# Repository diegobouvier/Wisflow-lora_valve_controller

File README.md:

# Wisflow-lora_valve_controller
Kicad proyecto for a LoRa remote valve controler actuator

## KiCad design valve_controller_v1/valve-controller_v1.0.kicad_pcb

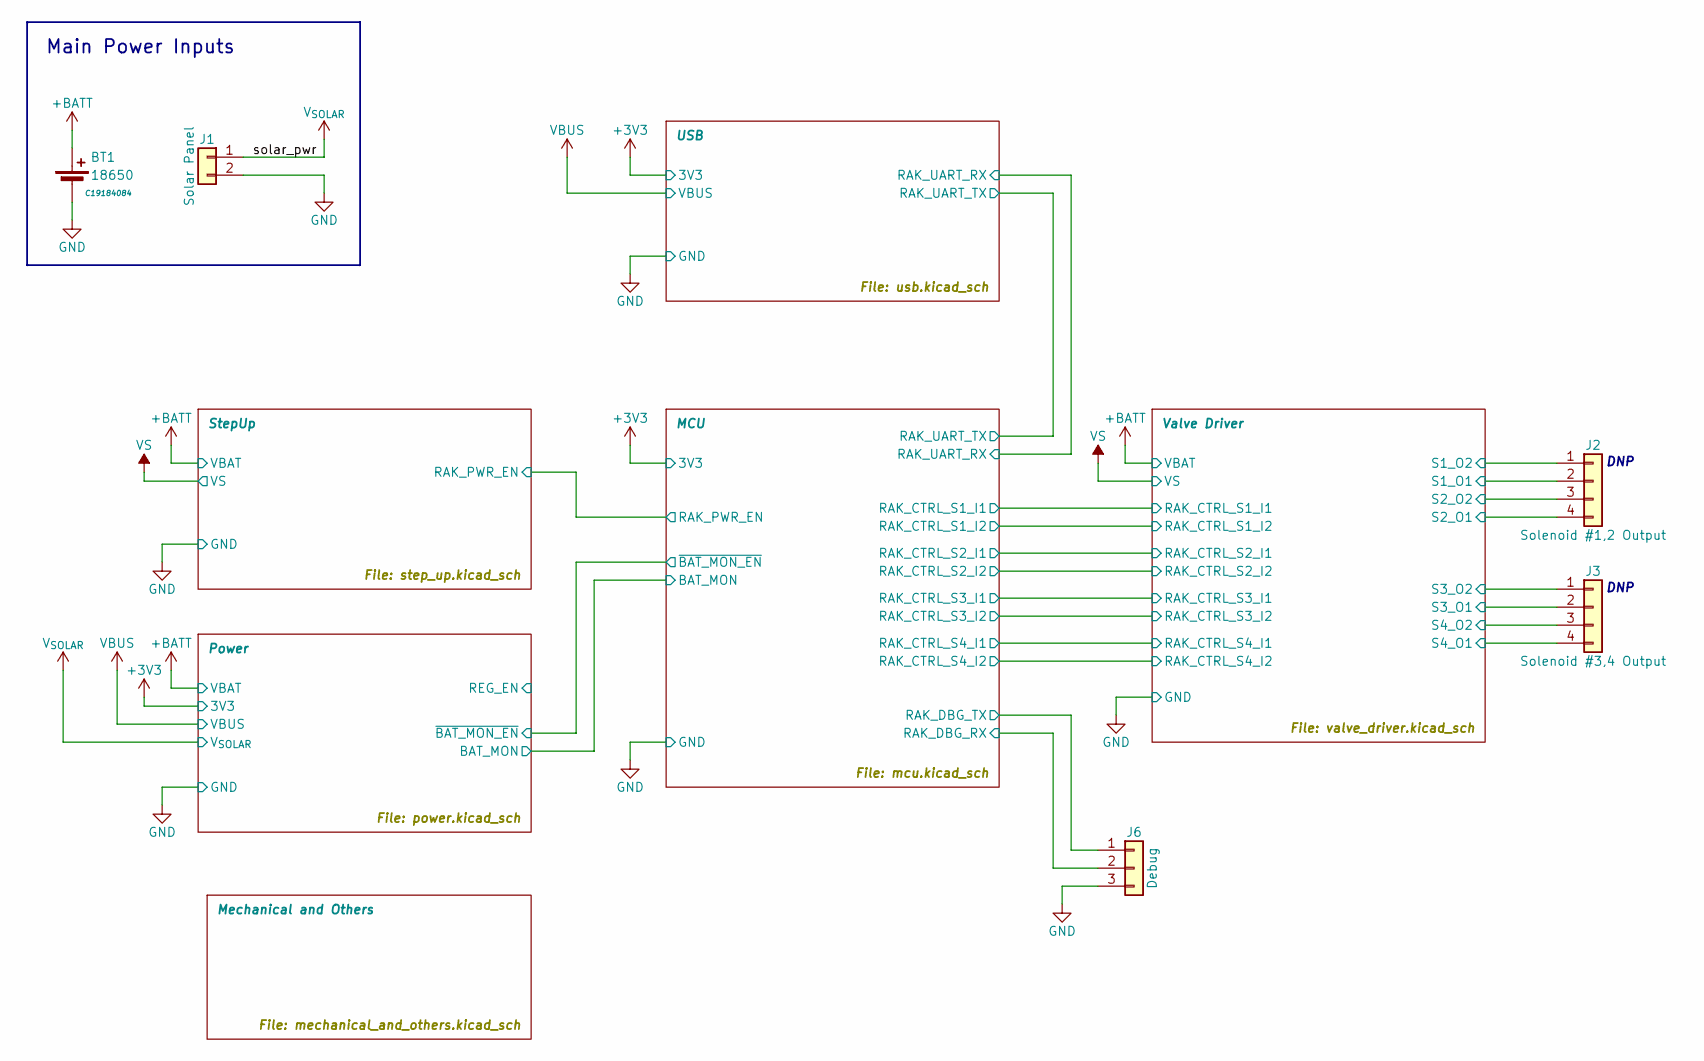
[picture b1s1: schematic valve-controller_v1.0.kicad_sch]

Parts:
BT1: 18650; BatteryHolder_MPD_BK-18650-PC2; JLCPCB C19184084
J1: Solar Panel; JST_PH_S2B-PH-SM4-TB_1x02-1MP_P2.00mm_Horizontal
J2: Solenoid #1,2 Output; 2EDGRM-5.08-04P
J3: Solenoid #3,4 Output; 2EDGRM-5.08-04P
J6: Debug; PinHeader_1x03_P2.54mm_Vertical

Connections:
+BATT: BT1.1 (+); also elsewhere on the board
/MCU/RAK_DBG_RX: J6.2; also elsewhere on the board
/MCU/RAK_DBG_TX: J6.1; also elsewhere on the board
/Valve Driver/S1_O1: J2.2; also elsewhere on the board
/Valve Driver/S1_O2: J2.1; also elsewhere on the board
/Valve Driver/S2_O1: J2.4; also elsewhere on the board
/Valve Driver/S2_O2: J2.3; also elsewhere on the board
/Valve Driver/S3_O1: J3.2; also elsewhere on the board
/Valve Driver/S3_O2: J3.1; also elsewhere on the board
/Valve Driver/S4_O1: J3.4; also elsewhere on the board
/Valve Driver/S4_O2: J3.3; also elsewhere on the board
GND: BT1.2 (-), J1.2, J6.3; also elsewhere on the board
V_{SOLAR}: J1.1; also elsewhere on the board

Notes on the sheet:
DNP
Main Power Inputs

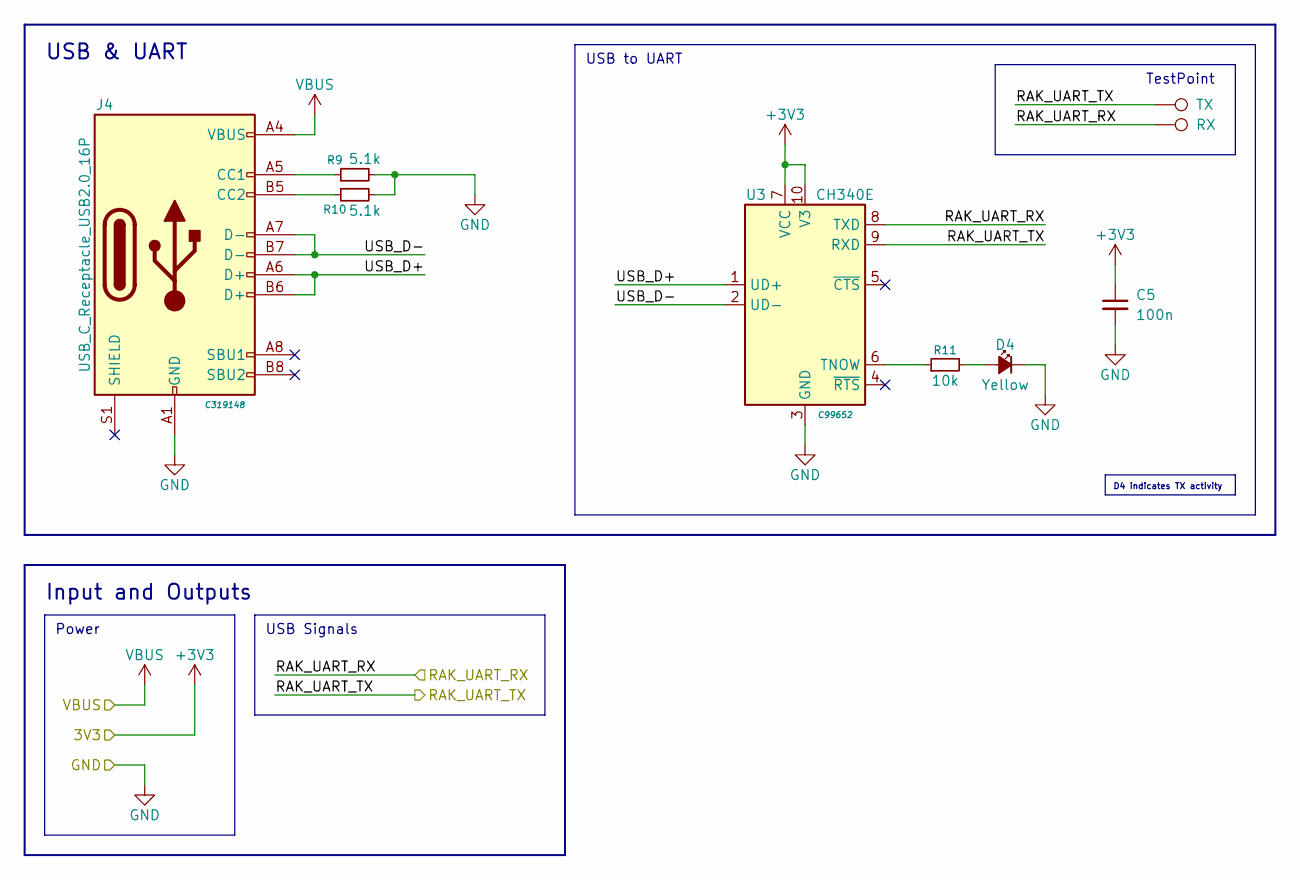
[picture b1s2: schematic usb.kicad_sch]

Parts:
C5: 100n; C_0603_1608Metric
D4: Yellow; LED_0603_1608Metric
J4: USB_C_Receptacle_USB2.0_16P; USB_C_Receptacle_GCT_USB4105-xx-A_16P_TopMnt_Horizontal; JLCPCB C319148
R9, R10: 5.1k; R_0603_1608Metric
R11: 10k; R_0603_1608Metric
TP7: TX; TestPoint_Pad_D1.0mm
TP8: RX; TestPoint_Pad_D1.0mm
U3: CH340E; MSOP-10_3x3mm_P0.5mm; JLCPCB C99652

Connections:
+3V3: C5.1, U3.7 (VCC), U3.10 (V3); also elsewhere on the board
/MCU/RAK_UART_RX: TP8.1 (1_1), U3.8 (TXD); also elsewhere on the board
/MCU/RAK_UART_TX: TP7.1 (1_1), U3.9 (RXD); also elsewhere on the board
/USB/USB_D+: J4.A6 (D+), J4.B6 (D+), U3.1 (UD+)
/USB/USB_D-: J4.A7 (D-), J4.B7 (D-), U3.2 (UD-)
GND: C5.2, D4.1 (K), J4.A1 (GND), J4.A12 (GND), J4.B1 (GND), J4.B12 (GND), R9.2, R10.2, U3.3 (GND); also elsewhere on the board
unnamed: D4.2 (A), R11.2
unnamed: J4.A5 (CC1), R9.1
unnamed: J4.B5 (CC2), R10.1
unnamed: R11.1, U3.6 (TNOW)
VBUS: J4.A4 (VBUS), J4.A9 (VBUS), J4.B4 (VBUS), J4.B9 (VBUS); also elsewhere on the board

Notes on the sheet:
USB to UART
Power
USB Signals
USB & UART
TestPoint
Input and Outputs
D4 indicates TX activity

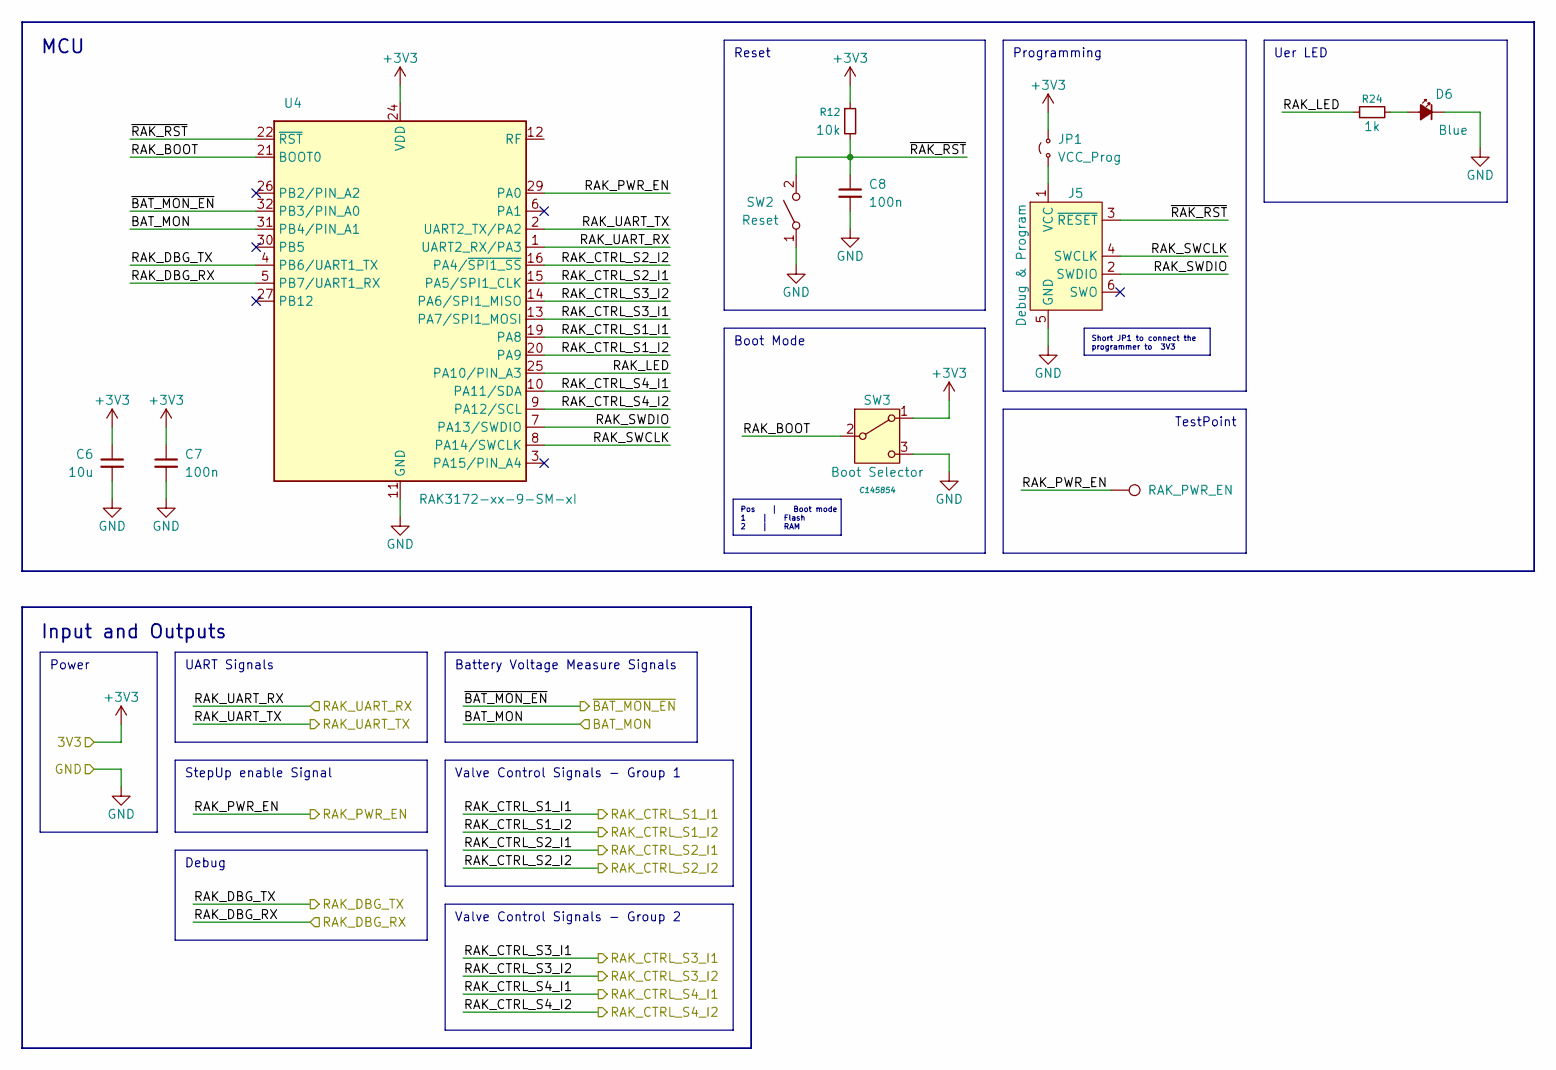
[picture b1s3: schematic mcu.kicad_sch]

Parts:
C6: 10u; C_0603_1608Metric
C7, C8: 100n; C_0603_1608Metric
D6: Blue; LED_0603_1608Metric
J5: Debug & Program; Tag-Connect_TC2030-IDC-NL_2x03_P1.27mm_Vertical
JP1: VCC_Prog; SolderJumper-2_P1.3mm_Bridged_Pad1.0x1.5mm
R12: 10k; R_0603_1608Metric
R24: 1k; R_0603_1608Metric
SW2: Reset; SW_SPST_B3U-1000P
SW3: Boot Selector; K3-1290S-E1; JLCPCB C145854
TP9: RAK_PWR_EN; TestPoint_Pad_D1.0mm
U4: RAK3172-xx-9-SM-xI; RAK3172

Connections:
+3V3: C6.1, C7.1, JP1.2 (B), R12.1, SW3.1 (A), U4.24 (VDD); also elsewhere on the board
/MCU/BAT_MON: U4.31 (PB4/PIN_A1); also elsewhere on the board
/MCU/RAK_BOOT: SW3.2 (B), U4.21 (BOOT0)
/MCU/RAK_CTRL_S1_I1: U4.19 (PA8); also elsewhere on the board
/MCU/RAK_CTRL_S1_I2: U4.20 (PA9); also elsewhere on the board
/MCU/RAK_CTRL_S2_I1: U4.15 (PA5/SPI1_CLK); also elsewhere on the board
/MCU/RAK_CTRL_S2_I2: U4.16 (PA4/~SPI1_SS); also elsewhere on the board
/MCU/RAK_CTRL_S3_I1: U4.13 (PA7/SPI1_MOSI); also elsewhere on the board
/MCU/RAK_CTRL_S3_I2: U4.14 (PA6/SPI1_MISO); also elsewhere on the board
/MCU/RAK_CTRL_S4_I1: U4.10 (PA11/SDA); also elsewhere on the board
/MCU/RAK_CTRL_S4_I2: U4.9 (PA12/SCL); also elsewhere on the board
/MCU/RAK_DBG_RX: U4.5 (PB7/UART1_RX); also elsewhere on the board
/MCU/RAK_DBG_TX: U4.4 (PB6/UART1_TX); also elsewhere on the board
/MCU/RAK_LED: R24.1, U4.25 (PA10/PIN_A3)
/MCU/RAK_PWR_EN: TP9.1 (1_1), U4.29 (PA0); also elsewhere on the board
/MCU/RAK_SWCLK: J5.4 (SWCLK), U4.8 (PA14/SWCLK)
/MCU/RAK_SWDIO: J5.2 (SWDIO), U4.7 (PA13/SWDIO)
/MCU/RAK_UART_RX: U4.1 (UART2_RX/PA3); also elsewhere on the board
/MCU/RAK_UART_TX: U4.2 (UART2_TX/PA2); also elsewhere on the board
/MCU/~BAT_MON_EN: U4.32 (PB3/PIN_A0); also elsewhere on the board
/MCU/~RAK_RST: C8.1, J5.3 (~RESET), R12.2, SW2.2 (B), U4.22 (~RST)
GND: C6.2, C7.2, C8.2, D6.1 (K), J5.5 (GND), SW2.1 (A), SW3.3 (C), U4.11 (GND), U4.17 (GND), U4.18 (GND), U4.23 (GND), U4.28 (GND); also elsewhere on the board
unnamed: D6.2 (A), R24.2
unnamed: J5.1 (VCC), JP1.1 (A)

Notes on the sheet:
Input and Outputs
Valve Control Signals - Group 1
Battery Voltage Measure Signals
MCU
Debug
Uer LED
Programming
Boot Mode
Reset
TestPoint
Valve Control Signals - Group 2
StepUp enable Signal
UART Signals
Power
Pos | Boot mode 1 | Flash 2 | RAM
Short JP1 to connect the programmer to 3V3

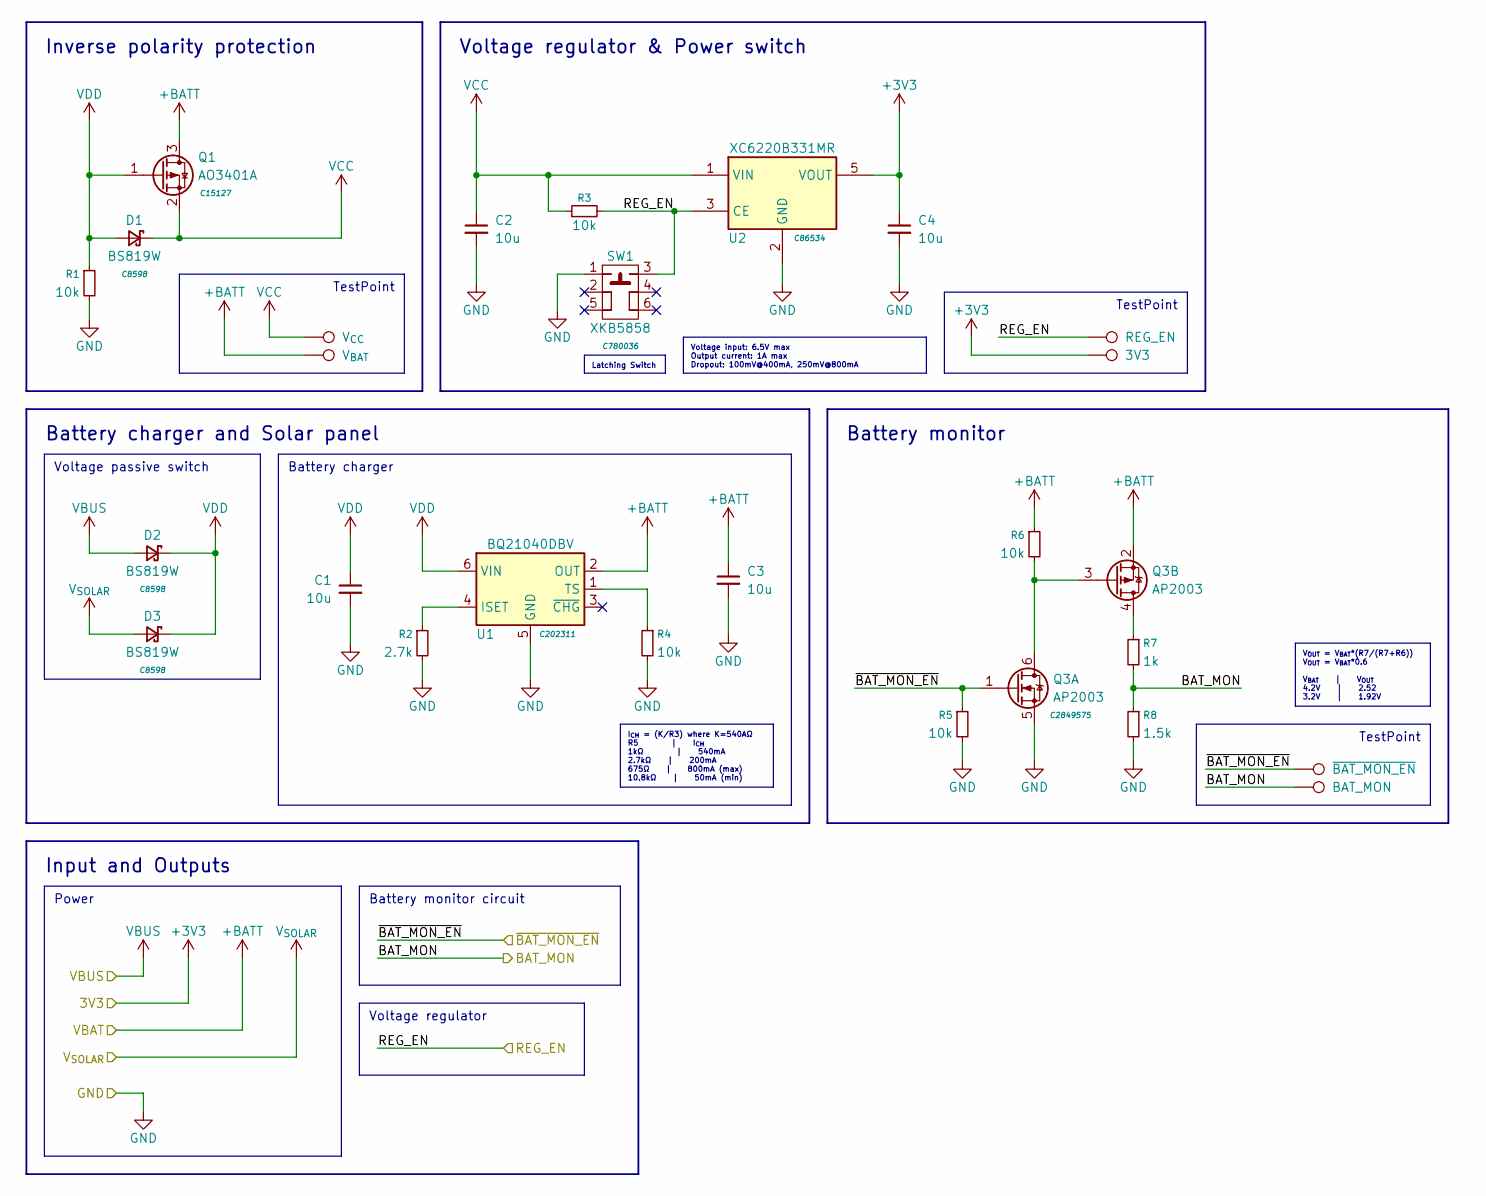
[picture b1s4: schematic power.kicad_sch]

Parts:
C1, C2, C3, C4: 10u; C_0603_1608Metric
D1, D2, D3: BS819W; D_SOD-123; JLCPCB C8598
Q1: AO3401A; SOT-23; JLCPCB C15127
Q3: AP2003; TSOT-23-6; JLCPCB C2849575
R1, R3, R4, R5, R6: 10k; R_0603_1608Metric
R2: 2.7k; R_0603_1608Metric
R7: 1k; R_0603_1608Metric
R8: 1.5k; R_0603_1608Metric
SW1: XKB5858; XKB5858-X-F-75; JLCPCB C780036
TP1: V_{CC}; TestPoint_Pad_D1.0mm
TP2: V_{BAT}; TestPoint_Pad_D1.0mm
TP3: REG_EN; TestPoint_Pad_D1.0mm
TP4: 3V3; TestPoint_Pad_D1.0mm
TP5: ~{BAT_MON_EN}; TestPoint_Pad_D1.0mm
TP6: BAT_MON; TestPoint_Pad_D1.0mm
U1: BQ21040DBV; SOT-23-6; JLCPCB C202311
U2: XC6220B331MR; SOT-23-5; JLCPCB C86534

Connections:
+3V3: C4.1, TP4.1 (1_1), U2.5 (VOUT); also elsewhere on the board
+BATT: C3.1, Q1.3 (D), Q3.2 (S), R6.1, TP2.1 (1_1), U1.2 (OUT); also elsewhere on the board
/MCU/BAT_MON: R7.2, R8.1, TP6.1 (1_1); also elsewhere on the board
/MCU/~BAT_MON_EN: Q3.1 (G), R5.1, TP5.1 (1_1); also elsewhere on the board
/Power/REG_EN: R3.2, SW1.3, TP3.1 (1_1), U2.3 (CE)
GND: C1.2, C2.2, C3.2, C4.2, Q3.5 (S), R1.2, R2.2, R4.2, R5.2, R8.2, SW1.1, U1.5 (GND), U2.2 (GND); also elsewhere on the board
unnamed: Q3.3 (G), Q3.6 (D), R6.2
unnamed: Q3.4 (D), R7.1
unnamed: R2.1, U1.4 (ISET)
unnamed: R4.1, U1.1 (TS)
VBUS: D2.2 (A); also elsewhere on the board
VCC: C2.1, D1.1 (K), Q1.2 (S), R3.1, TP1.1 (1_1), U2.1 (VIN)
VDD: C1.1, D1.2 (A), D2.1 (K), D3.1 (K), Q1.1 (G), R1.1, U1.6 (VIN)
V_{SOLAR}: D3.2 (A); also elsewhere on the board

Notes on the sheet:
Voltage regulator
Battery monitor circuit
Voltage regulator & Power switch
Input and Outputs
TestPoint
Inverse polarity protection
Battery charger and Solar panel
Voltage passive switch
Power
Battery charger
Battery monitor
I_{CH} = (K/R3) where K=540AΩ R5 | I_{CH} 1kΩ | 540mA 2.7kΩ | 200mA 675Ω | 800mA (max) 10.8kΩ | 50mA (min)
V_{OUT} = V_{BAT}*(R7/(R7+R6)) V_{OUT} = V_{BAT}*0.6 V_{BAT} | V_{OUT} 4.2V | 2.52 3.2V | 1.92V
Voltage input: 6.5V max Output current: 1A max Dropout: 100mV@400mA, 250mV@800mA
Latching Switch

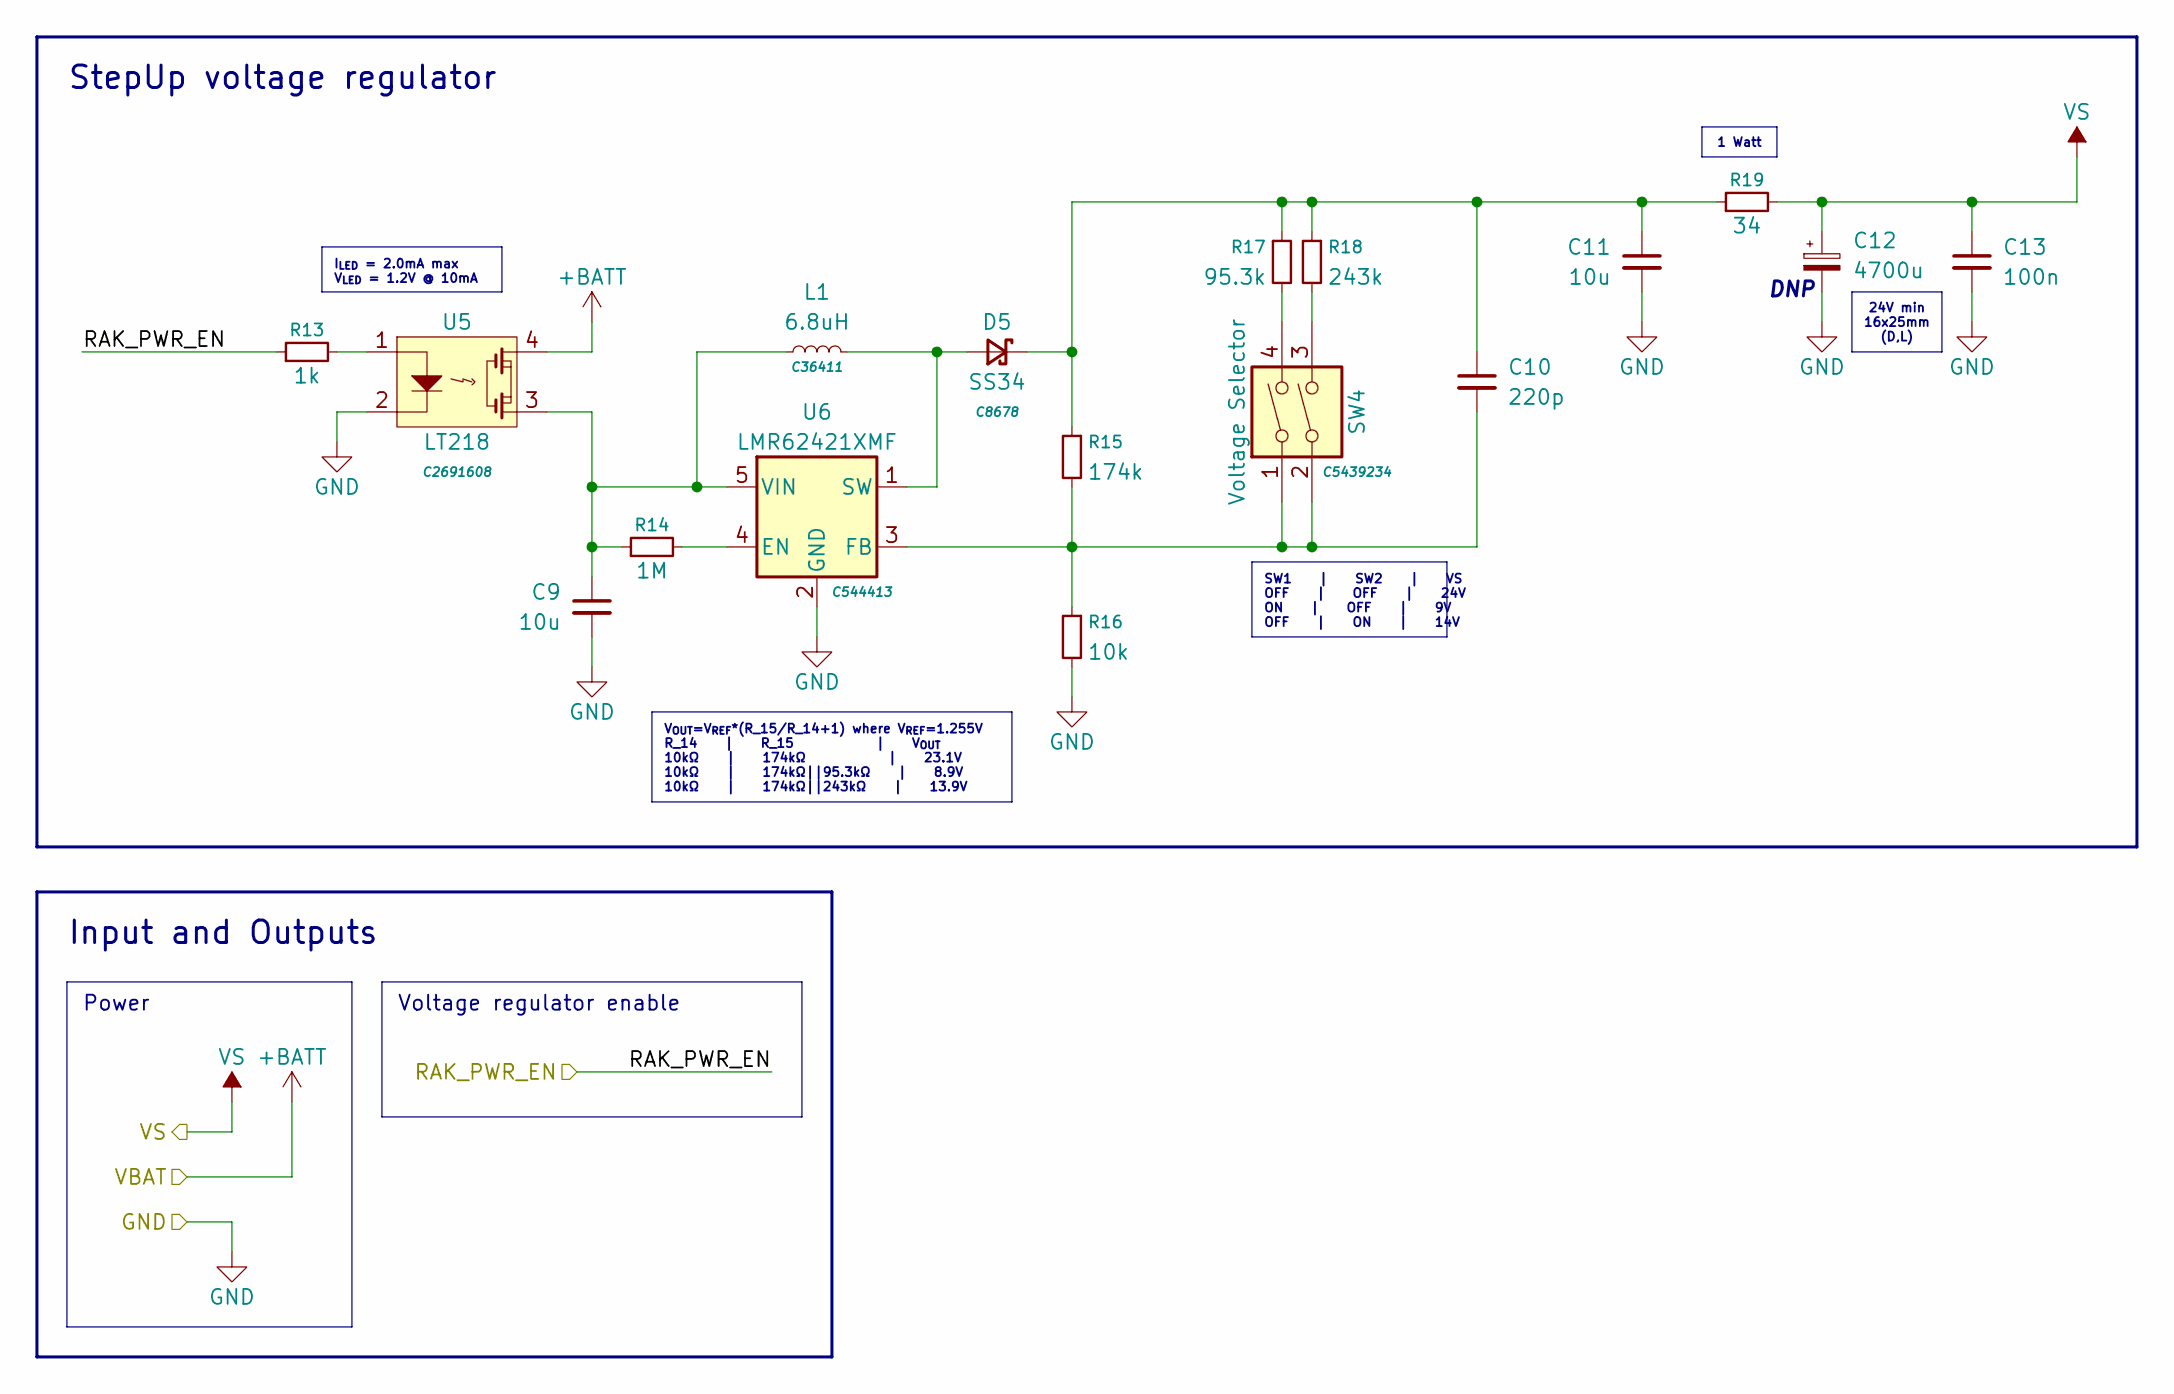
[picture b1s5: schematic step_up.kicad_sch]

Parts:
C9, C11: 10u; C_0603_1608Metric
C10: 220p; C_0603_1608Metric
C12: 4700u; CP_Horizontal_D16_L25_P7.5mm
C13: 100n; C_0603_1608Metric
D5: SS34; D_SMA; JLCPCB C8678
L1: 6.8uH; L_Sunlord_SWPA5040S; JLCPCB C36411
R13: 1k; R_0603_1608Metric
R14: 1M; R_0603_1608Metric
R15: 174k; R_0603_1608Metric
R16: 10k; R_0603_1608Metric
R17: 95.3k; R_0603_1608Metric
R18: 243k; R_0603_1608Metric
R19: 34; R_2512_6332Metric
SW4: Voltage Selector; SMXMS-02; JLCPCB C5439234
U5: LT218; SO-4_4.4x4.3mm_P2.54mm; JLCPCB C2691608
U6: LMR62421XMF; SOT-23-5; JLCPCB C544413

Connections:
+BATT: U5.4; also elsewhere on the board
/MCU/RAK_PWR_EN: R13.1; also elsewhere on the board
GND: C9.2, C11.2, C12.2, C13.2, R16.2, U5.2, U6.2 (GND); also elsewhere on the board
unnamed: D5.2 (A), L1.2, U6.1 (SW)
unnamed: C10.1, C11.1, D5.1 (K), R15.1, R17.1, R18.1, R19.1
unnamed: R13.2, U5.1
unnamed: R17.2, SW4.4
unnamed: R18.2, SW4.3
unnamed: R14.2, U6.4 (EN)
unnamed: C10.2, R15.2, R16.1, SW4.1, SW4.2, U6.3 (FB)
unnamed: C9.1, L1.1, R14.1, U5.3, U6.5 (VIN)
VS: C12.1, C13.1, R19.2; also elsewhere on the board

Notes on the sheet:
Voltage regulator enable
Input and Outputs
StepUp voltage regulator
DNP
Power
1 Watt
24V min 16x25mm (D,L)
V_{OUT}=V_{REF}*(R_15/R_14+1) where V_{REF}=1.255V R_14 | R_15 | V_{OUT} 10kΩ | 174kΩ | 23.1V 10kΩ | 174kΩ||95.3kΩ | 8.9V 10kΩ | 174kΩ||243kΩ | 13.9V
SW1 | SW2 | VS OFF | OFF | 24V ON | OFF | 9V OFF | ON | 14V
I_{LED} = 2.0mA max V_{LED} = 1.2V @ 10mA

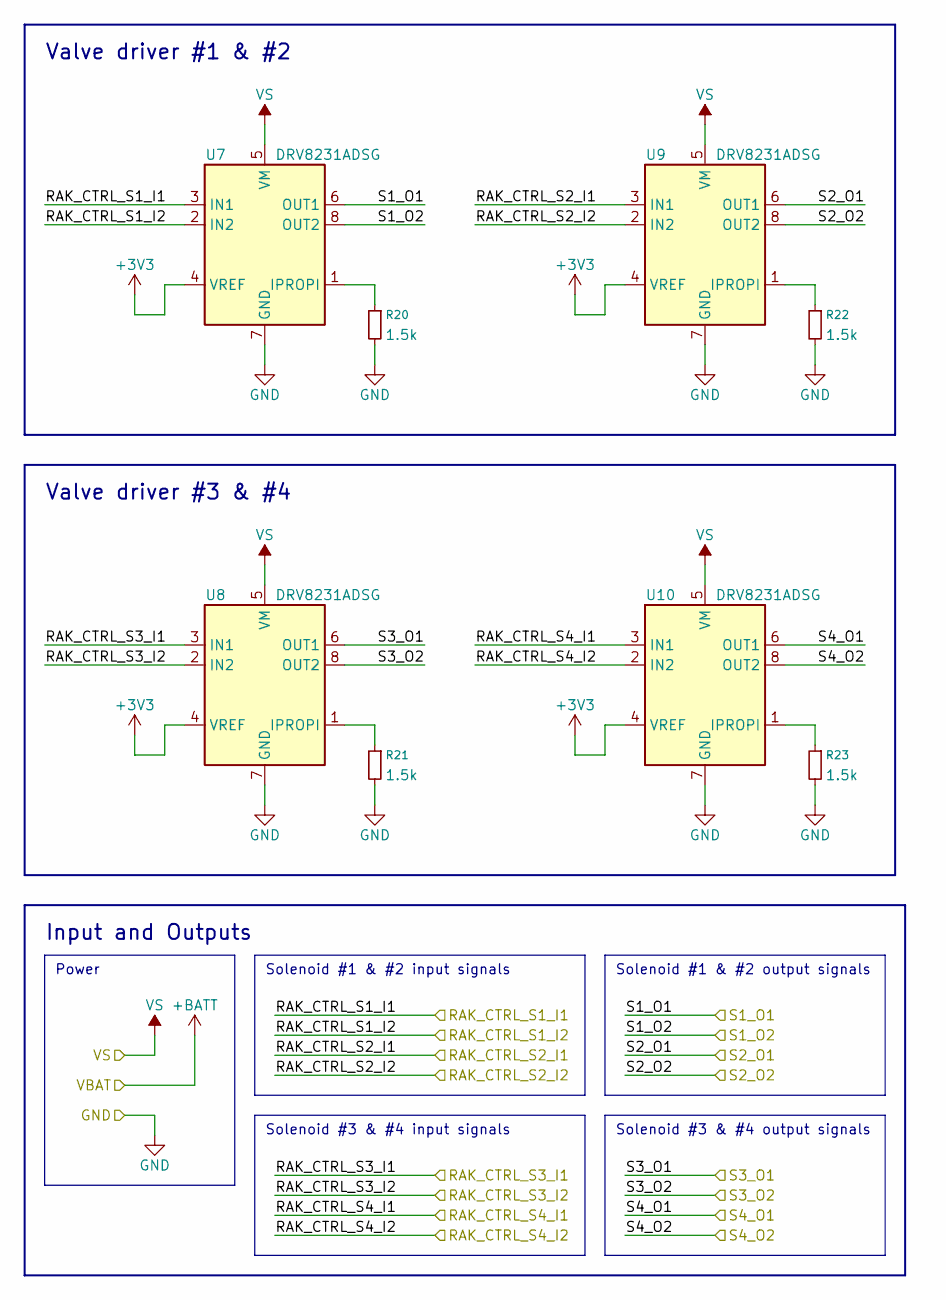
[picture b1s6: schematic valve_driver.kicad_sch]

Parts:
R20, R21, R22, R23: 1.5k; R_0603_1608Metric
U7, U8, U9, U10: DRV8231ADSG; WSON-8-1EP_2x2mm_P0.5mm_EP0.9x1.6mm

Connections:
+3V3: U7.4 (VREF), U8.4 (VREF), U9.4 (VREF), U10.4 (VREF); also elsewhere on the board
/MCU/RAK_CTRL_S1_I1: U7.3 (IN1); also elsewhere on the board
/MCU/RAK_CTRL_S1_I2: U7.2 (IN2); also elsewhere on the board
/MCU/RAK_CTRL_S2_I1: U9.3 (IN1); also elsewhere on the board
/MCU/RAK_CTRL_S2_I2: U9.2 (IN2); also elsewhere on the board
/MCU/RAK_CTRL_S3_I1: U8.3 (IN1); also elsewhere on the board
/MCU/RAK_CTRL_S3_I2: U8.2 (IN2); also elsewhere on the board
/MCU/RAK_CTRL_S4_I1: U10.3 (IN1); also elsewhere on the board
/MCU/RAK_CTRL_S4_I2: U10.2 (IN2); also elsewhere on the board
/Valve Driver/S1_O1: U7.6 (OUT1); also elsewhere on the board
/Valve Driver/S1_O2: U7.8 (OUT2); also elsewhere on the board
/Valve Driver/S2_O1: U9.6 (OUT1); also elsewhere on the board
/Valve Driver/S2_O2: U9.8 (OUT2); also elsewhere on the board
/Valve Driver/S3_O1: U8.6 (OUT1); also elsewhere on the board
/Valve Driver/S3_O2: U8.8 (OUT2); also elsewhere on the board
/Valve Driver/S4_O1: U10.6 (OUT1); also elsewhere on the board
/Valve Driver/S4_O2: U10.8 (OUT2); also elsewhere on the board
GND: R20.2, R21.2, R22.2, R23.2, U7.7 (GND), U7.9 (GND), U8.7 (GND), U8.9 (GND), U9.7 (GND), U9.9 (GND), U10.7 (GND), U10.9 (GND); also elsewhere on the board
unnamed: R20.1, U7.1 (IPROPI)
unnamed: R21.1, U8.1 (IPROPI)
unnamed: R22.1, U9.1 (IPROPI)
unnamed: R23.1, U10.1 (IPROPI)
VS: U7.5 (VM), U8.5 (VM), U9.5 (VM), U10.5 (VM); also elsewhere on the board

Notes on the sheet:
Solenoid #3 & #4 output signals
Power
Solenoid #3 & #4 input signals
Input and Outputs
Solenoid #1 & #2 output signals
Solenoid #1 & #2 input signals
Valve driver #1 & #2
Valve driver #3 & #4

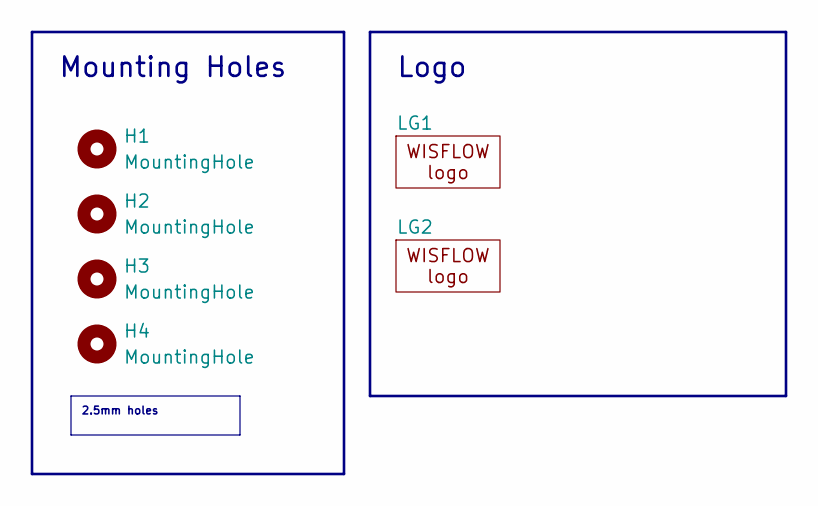
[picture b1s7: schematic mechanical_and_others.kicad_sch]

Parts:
H1, H2, H3, H4: MountingHole; MountingHole_2.5mm
LG1: WisflowLogo_30mm
LG2: WisflowLogo_20mm

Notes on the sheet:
Logo
Mounting Holes
2.5mm holes

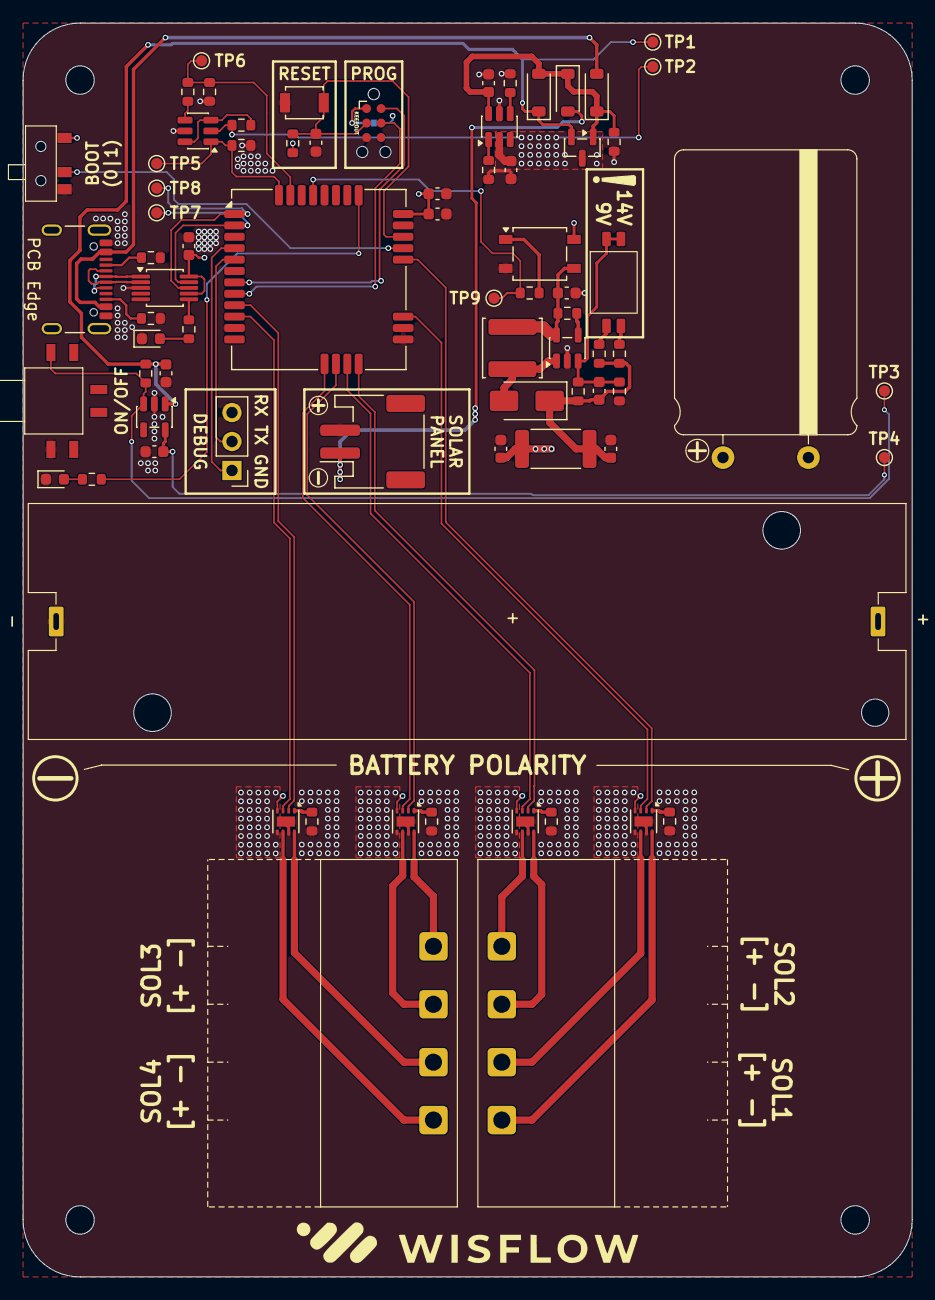
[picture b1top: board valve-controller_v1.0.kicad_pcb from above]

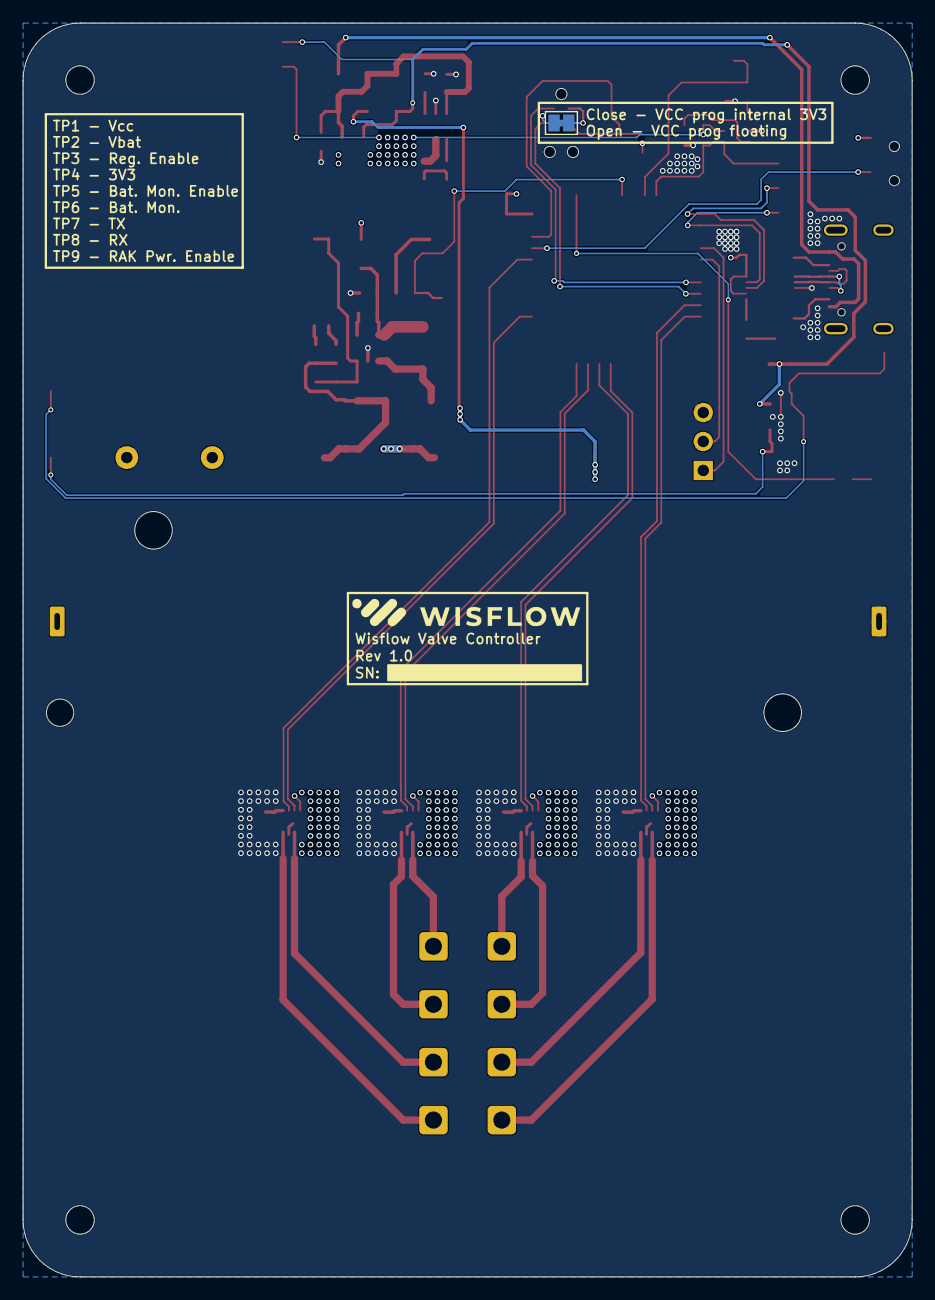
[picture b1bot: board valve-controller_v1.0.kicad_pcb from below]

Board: 4 copper layers, 78.0 x 110.0 mm, 83 parts (2 on the bottom side), 61 nets.

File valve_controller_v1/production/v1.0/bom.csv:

Designator,Footprint,Quantity,Value,LCSC Part #
BT1,BatteryHolder_MPD_BK-18650-PC2,1,18650,
"C1, C11, C2, C3, C4, C6, C9",0603,7,10u,
C10,0603,1,220p,
"C13, C5, C7, C8",0603,4,100n,
"D1, D2, D3",D_SOD-123,3,BS819W,
D4,0603,1,Yellow,
D5,D_SMA,1,SS34,
J1,JST_PH_S2B-PH-SM4-TB_1x02-1MP_P2.00mm_Horizontal,1,Solar Panel,
J4,USB_C_Receptacle_GCT_USB4105-xx-A_16P_TopMnt_Horizontal,1,USB_C_Receptacle_USB2.0_16P,
L1,L_Sunlord_SWPA5040S,1,6.8uH,
Q1,SOT-23,1,AO3401A,
Q3,TSOT-23-6,1,AP2003,
"R1, R11, R12, R16, R3, R4, R5, R6",0603,8,10k,
"R10, R9",0603,2,5.1k,
"R13, R7",0603,2,1k,
R14,0603,1,1M,
R15,0603,1,174k,
R17,0603,1,95.3k,
R18,0603,1,243k,
R19,2512,1,34,
R2,0603,1,2.7k,
"R20, R21, R22, R23, R8",0603,5,1.5k,
SW1,XKB5858-X-F-75,1,XKB5858,
SW2,SW_SPST_B3U-1000P,1,Reset,
SW3,K3-1290S-E1,1,Boot Selector,
SW4,SMXMS-02,1,Voltage Selector,
U1,SOT-23-6,1,BQ21040DBV,
"U10, U7, U8, U9",WSON-8-1EP_2x2mm_P0.5mm_EP0.9x1.6mm,4,DRV8231ADSG,
U2,SOT-23-5,1,XC6220B331MR,
U3,MSOP-10_3x3mm_P0.5mm,1,CH340E,
U4,RAK3172,1,RAK3172-xx-9-SM-xI,
U5,SO-4_4.4x4.3mm_P2.54mm,1,LT218,
U6,SOT-23-5,1,LMR62421XMF,

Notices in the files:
parts and their libraries:
Copyright 2021 Accelerated Designs. All rights reserved.
